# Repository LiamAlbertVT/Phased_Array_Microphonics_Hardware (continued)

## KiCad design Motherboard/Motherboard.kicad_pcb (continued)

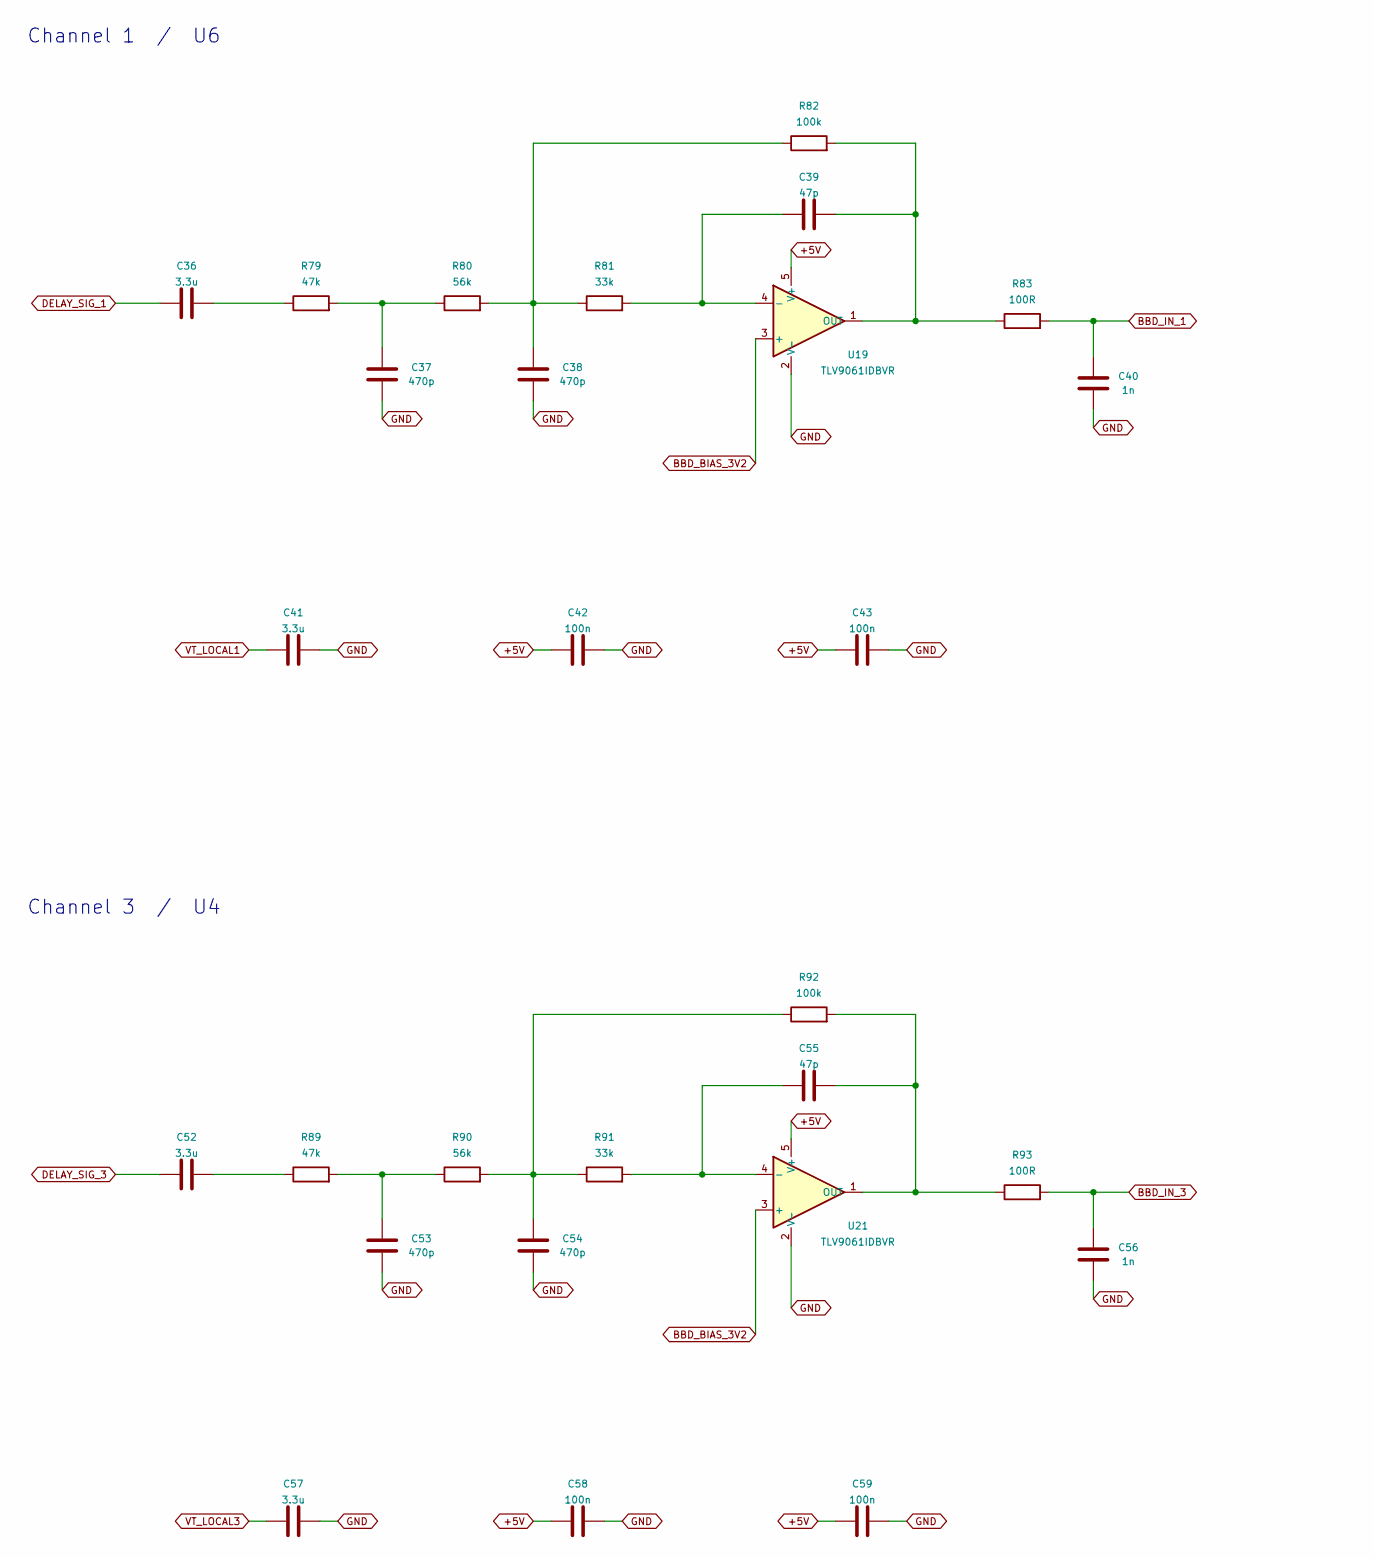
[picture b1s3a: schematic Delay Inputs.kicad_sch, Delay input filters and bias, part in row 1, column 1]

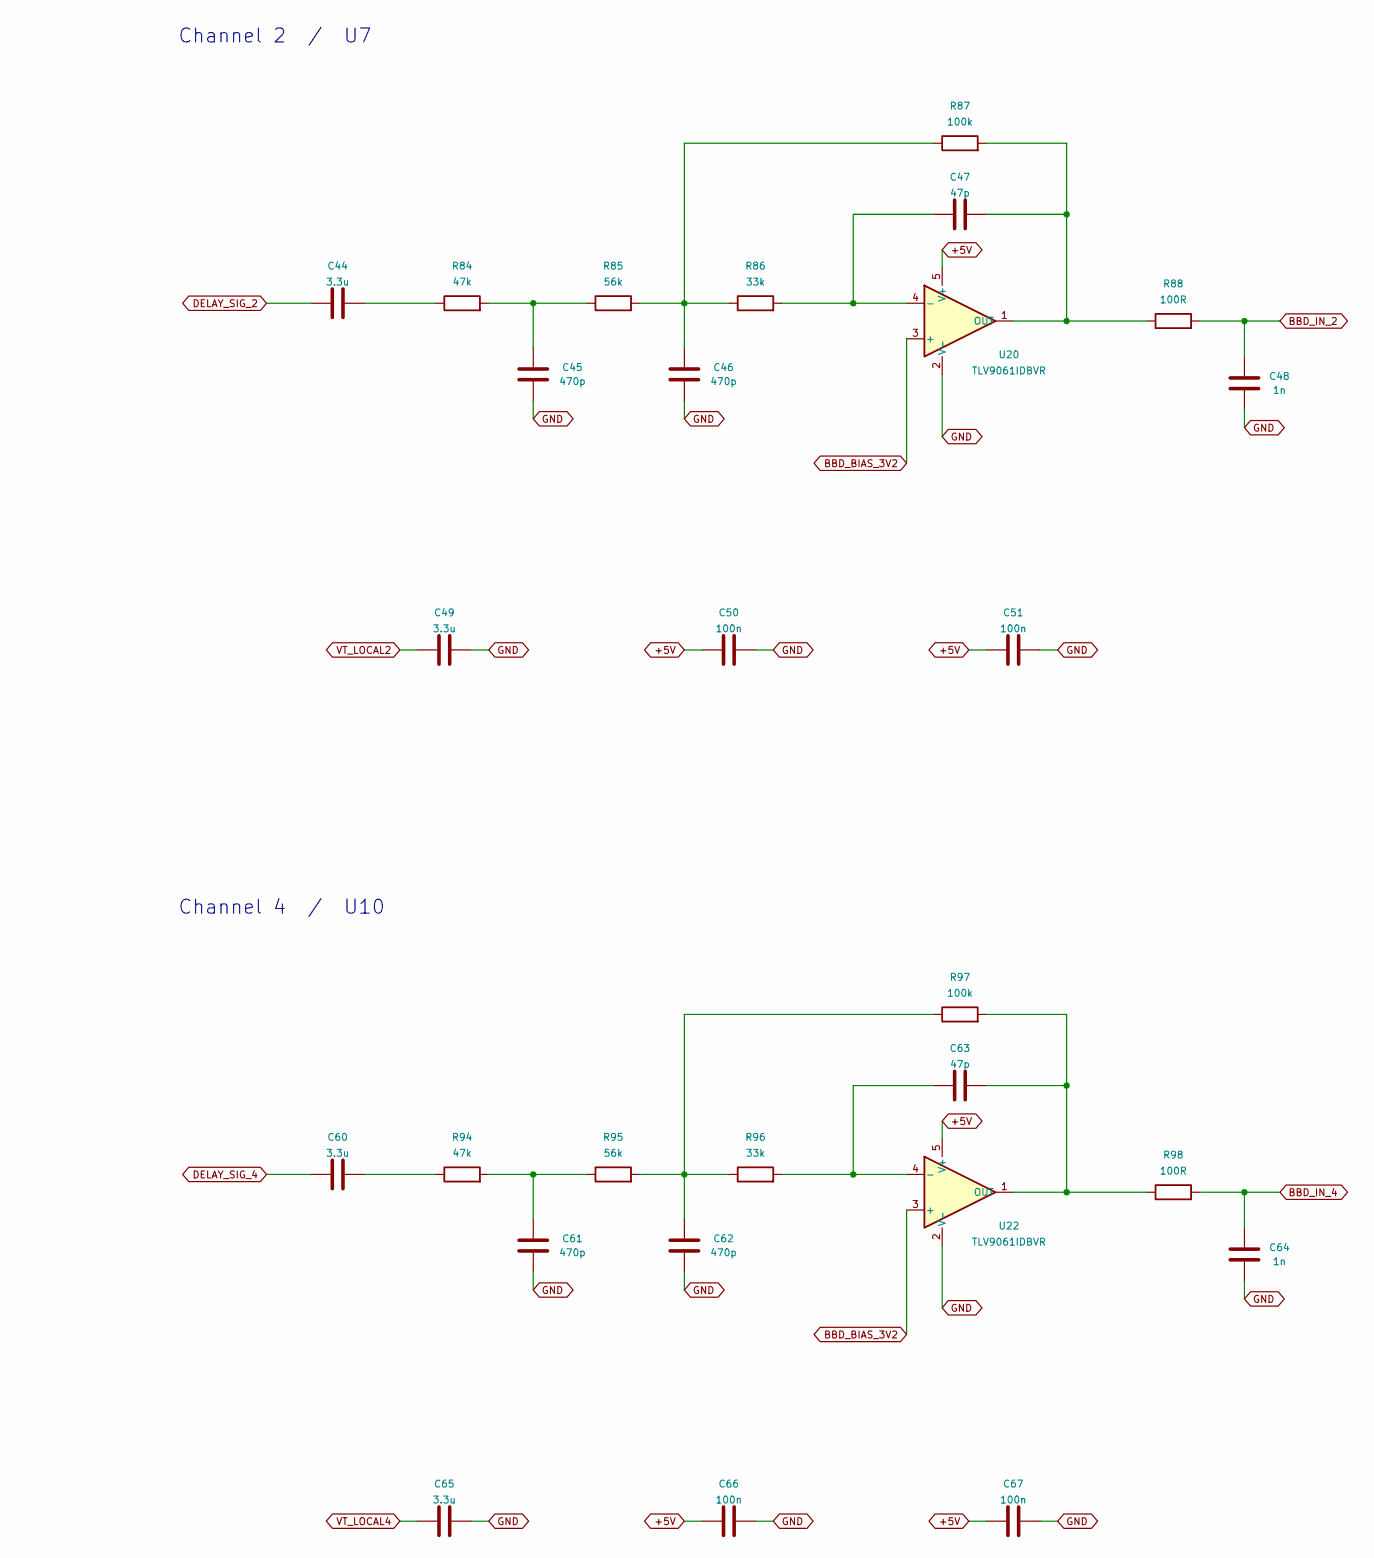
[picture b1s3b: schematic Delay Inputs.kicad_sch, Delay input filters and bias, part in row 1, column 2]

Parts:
C36, C41, C44, C49, C52, C57, C60, C65: 3.3u; C_0805_2012Metric
C37, C38, C45, C46, C53, C54, C61, C62: 470p; C_0603_1608Metric
C39, C47, C55, C63: 47p; C_0603_1608Metric
C40, C48, C56, C64: 1n; C_0603_1608Metric
C42, C43, C50, C51, C58, C59, C66, C67: 100n; C_0603_1608Metric
R79, R84, R89, R94: 47k; R_0603_1608Metric
R80, R85, R90, R95: 56k; R_0603_1608Metric
R81, R86, R91, R96: 33k; R_0603_1608Metric
R82, R87, R92, R97: 100k; R_0603_1608Metric
R83, R88, R93, R98: 100R; R_0603_1608Metric
U19, U20, U21, U22: TLV9061IDBVR; SOT-23-5

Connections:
+5V: C42.1, C43.1, C50.1, C51.1, C58.1, C59.1, C66.1, C67.1, U19.5 (V+), U20.5 (V+), U21.5 (V+), U22.5 (V+); also elsewhere on the board
BBD_BIAS_3V2: U19.3 (+), U20.3 (+), U21.3 (+), U22.3 (+); also elsewhere on the board
BBD_IN_1: C40.1, R83.2; also elsewhere on the board
BBD_IN_2: C48.1, R88.2; also elsewhere on the board
BBD_IN_3: C56.1, R93.2; also elsewhere on the board
BBD_IN_4: C64.1, R98.2; also elsewhere on the board
DELAY_SIG_1: C36.1; also elsewhere on the board
DELAY_SIG_2: C44.1; also elsewhere on the board
DELAY_SIG_3: C52.1; also elsewhere on the board
DELAY_SIG_4: C60.1; also elsewhere on the board
GND: C37.2, C38.2, C40.2, C41.2, C42.2, C43.2, C45.2, C46.2, C48.2, C49.2, C50.2, C51.2, C53.2, C54.2, C56.2, C57.2, C58.2, C59.2, C61.2, C62.2, C64.2, C65.2, C66.2, C67.2, U19.2 (V-), U20.2 (V-), U21.2 (V-), U22.2 (V-); also elsewhere on the board
unnamed: C36.2, R79.1
unnamed: C37.1, R79.2, R80.1
unnamed: C38.1, R80.2, R81.1, R82.1
unnamed: C44.2, R84.1
unnamed: C45.1, R84.2, R85.1
unnamed: C46.1, R85.2, R86.1, R87.1
unnamed: C52.2, R89.1
unnamed: C53.1, R89.2, R90.1
unnamed: C54.1, R90.2, R91.1, R92.1
unnamed: C60.2, R94.1
unnamed: C61.1, R94.2, R95.1
unnamed: C62.1, R95.2, R96.1, R97.1
unnamed: C39.1, R81.2, U19.4 (-)
unnamed: C39.2, R82.2, R83.1, U19.1 (OUT)
unnamed: C47.1, R86.2, U20.4 (-)
unnamed: C47.2, R87.2, R88.1, U20.1 (OUT)
unnamed: C55.1, R91.2, U21.4 (-)
unnamed: C55.2, R92.2, R93.1, U21.1 (OUT)
unnamed: C63.1, R96.2, U22.4 (-)
unnamed: C63.2, R97.2, R98.1, U22.1 (OUT)
VT_LOCAL1: C41.1; also elsewhere on the board
VT_LOCAL2: C49.1; also elsewhere on the board
VT_LOCAL3: C57.1; also elsewhere on the board
VT_LOCAL4: C65.1; also elsewhere on the board

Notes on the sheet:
Channel 1 / U6
Channel 2 / U7
Channel 3 / U4
Channel 4 / U10

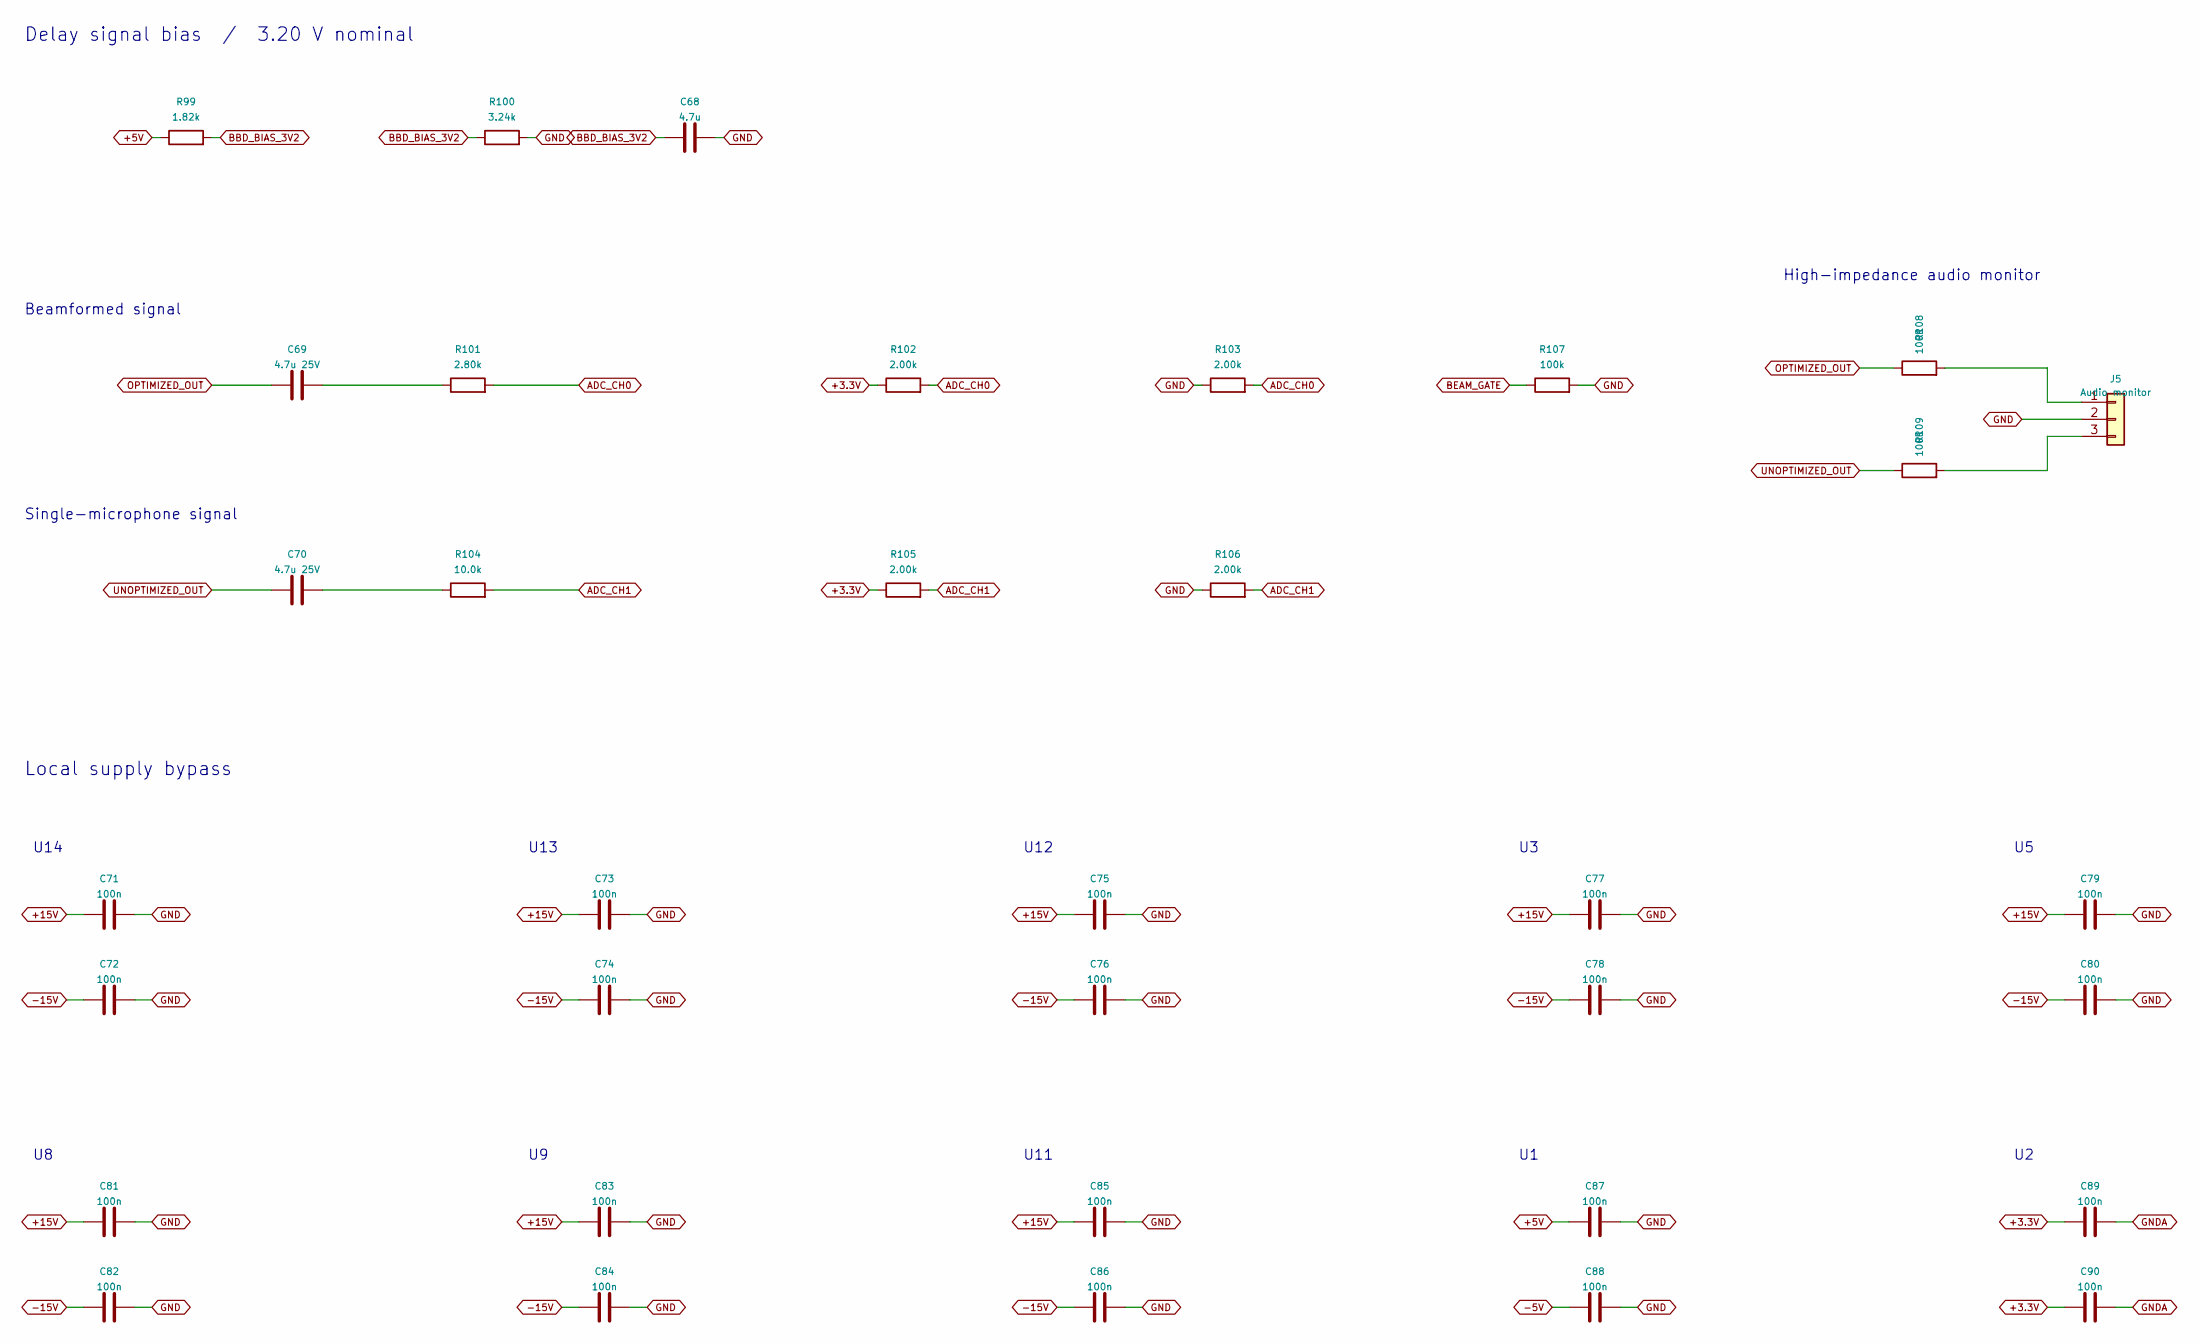
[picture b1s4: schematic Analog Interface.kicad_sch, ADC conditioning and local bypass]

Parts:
C68: 4.7u; C_0805_2012Metric
C69, C70: 4.7u 25V; C_0805_2012Metric
C71, C72, C73, C74, C75, C76, C77, C78, C79, C80, C81, C82, C83, C84, C85, C86, C87, C88, C89, C90: 100n; C_0603_1608Metric
J5: Audio monitor; PinHeader_1x03_P2.54mm_Vertical
R99: 1.82k; R_0603_1608Metric
R100: 3.24k; R_0603_1608Metric
R101: 2.80k; R_0603_1608Metric
R102, R103, R105, R106: 2.00k; R_0603_1608Metric
R104: 10.0k; R_0603_1608Metric
R107: 100k; R_0603_1608Metric
R108, R109: 100R; R_0603_1608Metric

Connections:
+3.3V: C89.1, C90.1, R102.1, R105.1; also elsewhere on the board
+5V: C87.1, R99.1; also elsewhere on the board
+15V: C71.1, C73.1, C75.1, C77.1, C79.1, C81.1, C83.1, C85.1; also elsewhere on the board
-5V: C88.1; also elsewhere on the board
-15V: C72.1, C74.1, C76.1, C78.1, C80.1, C82.1, C84.1, C86.1; also elsewhere on the board
ADC_CH0: R101.2, R102.2, R103.2; also elsewhere on the board
ADC_CH1: R104.2, R105.2, R106.2; also elsewhere on the board
BBD_BIAS_3V2: C68.1, R99.2, R100.1; also elsewhere on the board
BEAM_GATE: R107.1; also elsewhere on the board
GND: C68.2, C71.2, C72.2, C73.2, C74.2, C75.2, C76.2, C77.2, C78.2, C79.2, C80.2, C81.2, C82.2, C83.2, C84.2, C85.2, C86.2, C87.2, C88.2, J5.2, R100.2, R103.1, R106.1, R107.2; also elsewhere on the board
GNDA: C89.2, C90.2; also elsewhere on the board
unnamed: C69.2, R101.1
unnamed: C70.2, R104.1
unnamed: J5.1, R108.2
unnamed: J5.3, R109.2
OPTIMIZED_OUT: C69.1, R108.1; also elsewhere on the board
UNOPTIMIZED_OUT: C70.1, R109.1; also elsewhere on the board

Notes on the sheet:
Delay signal bias / 3.20 V nominal
Beamformed signal
Single-microphone signal
U14
U13
U12
U11
Local supply bypass
High-impedance audio monitor

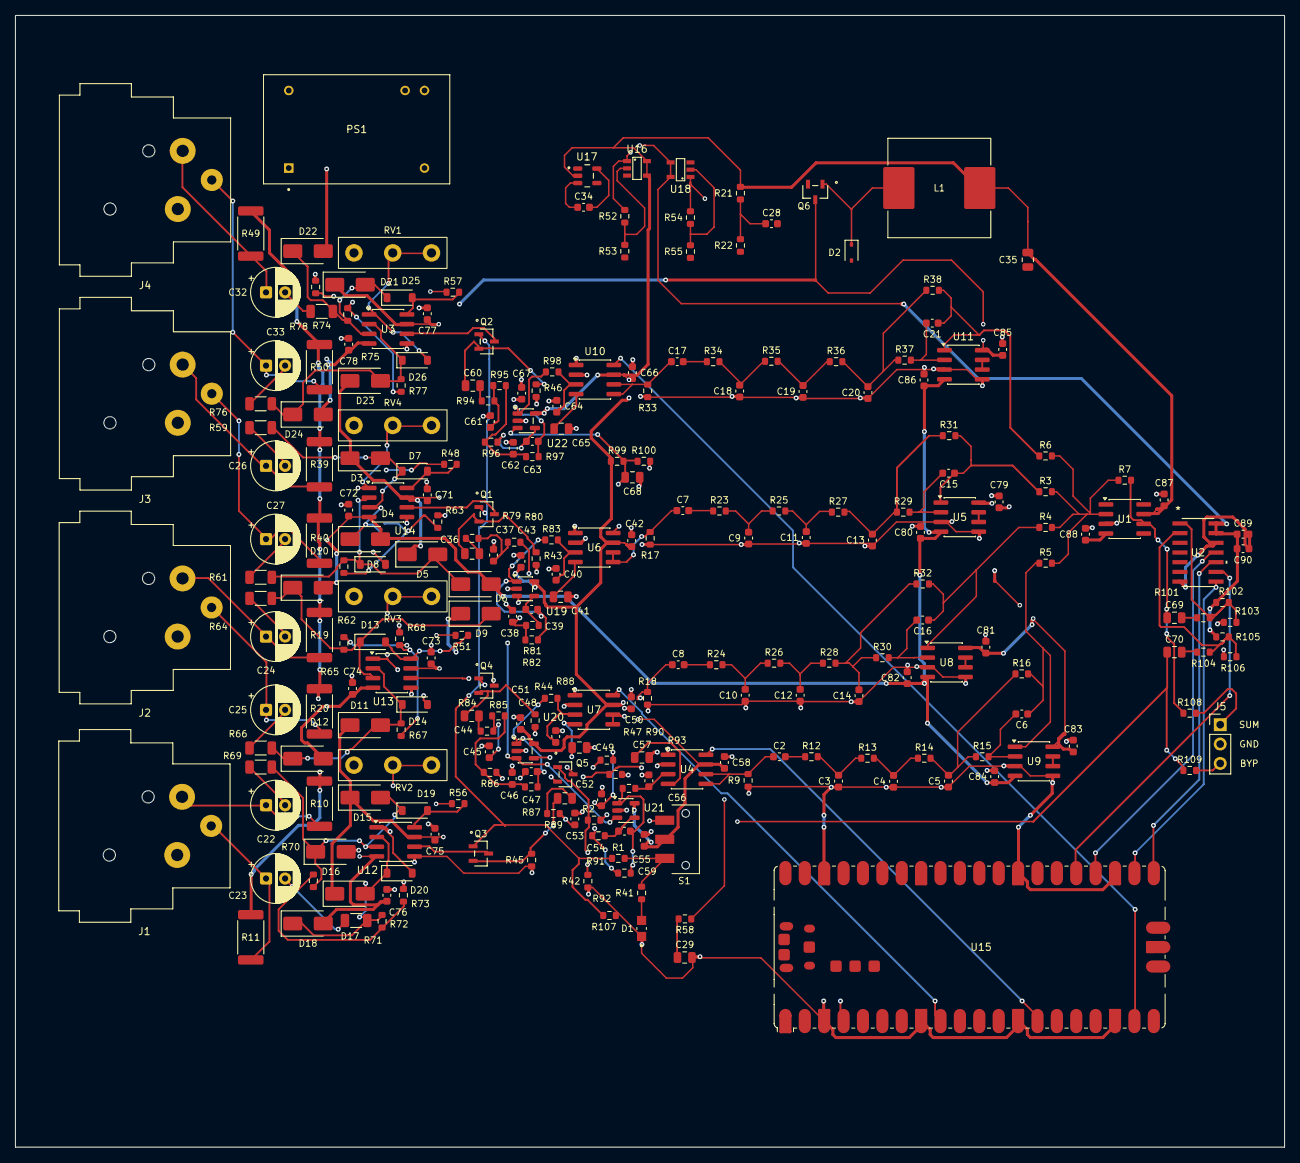
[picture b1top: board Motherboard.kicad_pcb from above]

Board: 4 copper layers, 166.2 x 148.2 mm, 261 parts (1 on the bottom side), 148 nets.

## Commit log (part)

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2026-01-29 Added high-level diagram & updated schematic
2026-01-29 Added README
2026-02-03 Updated schematic with additional logic and new symbols
2026-02-06 Fixed erroneous logic, added new ICs, and expanded circuit
2026-02-06 Revise README with recent updates and TODO items
    Updated recent updates and TODO sections with new findings and tasks.
2026-02-06 Added new Images directory and slightly modified BBD symbol
2026-02-06 Necessary logic fix (delay ALL signals, not just 3/4)
2026-02-06 Revise SSI2100 IC details in README
2026-02-09 Add ADC datasheet link
    Add link to ADC datasheet in README.
2026-02-13 Added microphone array circuitry and general improvements
2026-02-20 Completed design draft.
2026-02-25 Updated schematic with component values and improved logic
2026-03-09 Intermediate commit (should really make a branch but I'm too lazy)
2026-03-11 Completed schematic design.
2026-03-15 Added most footprints & updated parts list
2026-03-19 Schematic revisions & PCB generation
2026-03-19 Fix typo in 'Upcoming' section of README
2026-03-26 Resolved footprint errors and added slight schematic modifications
2026-03-26 Revise README with schematic updates and future plans
    Updated README with recent schematic modifications and resolved footprint errors. Added future plans for documentation and communication with Raspberry Pi Pico.
2026-03-31 Component placement draft
2026-04-03 Routed XLR output, switching, and summation stages.
2026-04-10 Most traces completed
2026-05-04 Added documentation and slight schematic modifications for logic.
2026-05-06 Revise README with updates and documentation
    Updated recent updates section with schematic revisions and added design documentation.
